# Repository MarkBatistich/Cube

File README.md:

# Cube

## Dynamic Model

To start, I drew a model of the sytem and defined some variables.

$\theta_w$ - angle of the wheel

$\theta_f$ - angle of the frame

$T$ - motor torque

$C_w$ - motor friction torque coefficient

$C_f$ - frame friction torque coefficient

$F_w$ - force of gravity on the wheel

$F_f$ - force of gravity on the frame

$I_c^o$ - moment of inertia of the cube about the origin

$I_w$ - moment of inertia of the wheel about its center of mass

$M_c^o$ - moment on the cube about the origin

$M_w$ - moment of the wheel about its center of mass

$m_w$ - mass of the wheel

$m_f$ - mass of the frame

$m_c$ - mass of the cube

$l_w$ - distance between the wheel's center of mass and the origin

$l_f$ - distance between the frame's center of mass and the origin

$l_c$ - distance between the cube's center of mass and the origin

I also defined the intertial axis such that +x is parellel to an unsloped surface and parallel to the cube face, +y is normal to an unsloped surface in the opposite direction as the force of gravity, and +z is in the direction of counterclockwise (CCW) wheel rotation. The origin O is placed at the corner of the cube touching the surface.

The equations of motion are constructed from the moments.

$M_c^o = I_c^o\ddot{\theta}_f = m_cl_cgsin(\theta_f) - (T - C_w\dot{\theta_w})-C_f\dot{\theta}_f$

$M_w = I_w(\ddot{\theta}_f+\ddot{\theta}_w) = T-C_w\dot{\theta_w}$

The cube moment of inertia about the origin can be found from the parallel axis theorem.

$I_c^o = I_f^o + I_w^o = I_f+m_fl_f^2 + I_w+m_wl_w^2$

The moment equations are solved for angular acceleration

$\ddot{\theta}_f = \frac{m_cl_cgsin(\theta_f)-T+C_w\dot{\theta_w}-C_f\dot{\theta}_f}{I_c^o}$

$\ddot{\theta}_w = \frac{T- C_w\dot{\theta_w}}{I_w} - \ddot{\theta}f$

From these equations, a state space model is made:

$x_1=\theta_f, x_2=\dot{\theta}_f,x_3=\dot{\theta}_w$

\dot{x}_1 = x_2$

$\dot{x}_2 = \frac{m_cl_cgsin(\theta_f)-T+C_w\dot{\theta_w}-C_f\dot{\theta}_f}{I_c^o}$

$\dot{x}_3 = \frac{T- C_w\dot{\theta_w}}{I_w} - \frac{m_cl_cgsin(\theta_f)-T+C_w\dot{\theta_w}-C_f\dot{\theta}_f}{I_c^o}$

The small angle approximation is applied: $\sin({\theta}_f)={\theta}_f$

The torque is related to the pwm input $u$ by the equation:

$T = K_tu$

where $K_t$ is the motor torque constant and $u$ is the applied PWM input to the motor on the range of $[-1, 1]$.

The state space equations are put into matrix form:

$\begin{bmatrix}
\dot{x}_1 \cr
\dot{x}_2 \cr
\dot{x}_3 
\end{bmatrix} = 
\begin{bmatrix}
0 & 1 & 0\cr
\frac{m_cl_cg}{I_c^o} & -\frac{C_f}{I_c^o} & \frac{C_w}{I_c^o}\cr
-\frac{m_cl_cg}{I_c^o} & \frac{C_f}{I_c^o} & -\frac{C_w}{I_w}-\frac{C_w}{I_c^o}
\end{bmatrix}
\begin{bmatrix}
x_1 \cr
x_2 \cr
x_3 
\end{bmatrix} + 
\begin{bmatrix}
0 \\
-\frac{K_t}{I_c^o} \\
\frac{K_t}{I_w}-\frac{K_t}{I_c^o}
\end{bmatrix} u $

Now all these values had to be determined. For better scaling, the gcs units were used (grams, centimeters, seconds):

$ g = 981 [\frac{cm}{s^2}]$

$m_c = 710\ [g]$

$l_c = 6.28\ [cm]$

$I_c^o = 37200\ [g*cm^2]$

$I_w = 2740 \ [g*cm^2]$

$C_f = 0$

$C_w = 0$

$K_t = 250000\ [\frac{g*cm^2}{s^2}]$

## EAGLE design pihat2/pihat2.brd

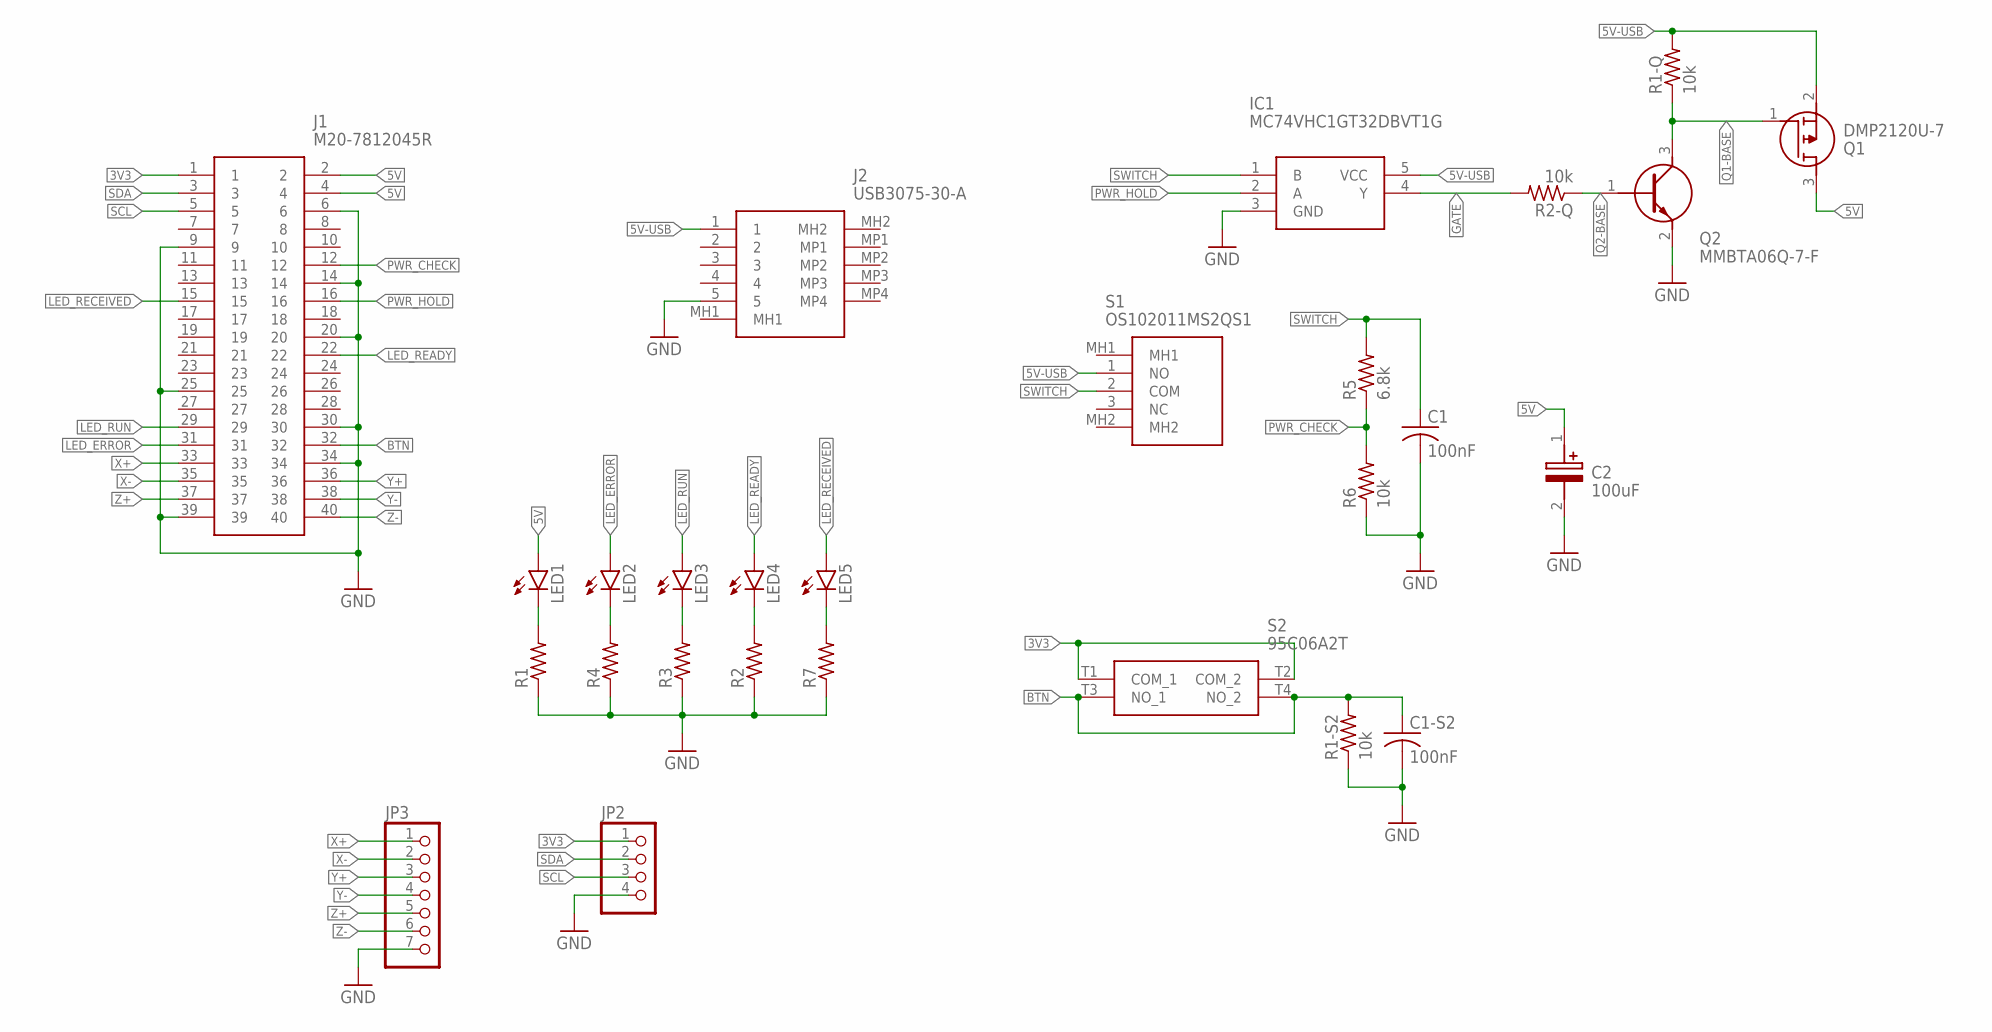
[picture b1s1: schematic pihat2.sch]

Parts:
C1, C1-S2: 100nF; C0805
C2: 100uF; CAPPRD250W45D630H500
IC1: MC74VHC1GT32DBVT1G
J1: M20-7812045R; M207812045R
J2: USB3075-30-A; USB307530A
JP2: PINHD-1X4; 1X04
JP3: PINHD-1X7; 1X07
LED1, LED2, LED3, LED4, LED5: LED5MM
Q1: DMP2120U-7; SOT96P240X110-3N
Q2: MMBTA06Q-7-F; SOT95P240X120-3N
R1, R2, R3, R4, R7: R-US_R0805; R0805
R1-Q, R1-S2, R2-Q, R6: 10k; R0805
R5: 6.8k; R0805
S1: OS102011MS2QS1
S2: 95C06A2T

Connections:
3V3: J1.1, JP2.1, S2.T1 (COM_1), S2.T2 (COM_2)
5V: C2.1 (+), J1.2, J1.4, LED1.A, Q1.3 (D)
5V-USB: IC1.5 (VCC), J2.1, Q1.2 (S), R1-Q.2, S1.1 (NO)
BTN: C1-S2.1, J1.32, R1-S2.2, S2.T3 (NO_1), S2.T4 (NO_2)
GATE: IC1.4 (Y), R2-Q.2
GND: C1.2, C1-S2.2, C2.2 (-), IC1.3 (GND), J1.6, J1.9, J1.14, J1.20, J1.25, J1.30, J1.34, J1.39, J2.5, JP2.4, JP3.7, Q2.2 (E), R1.1, R1-S2.1, R2.1, R3.1, R4.1, R6.1, R7.1
LED_ERROR: J1.31, LED2.A
LED_READY: J1.22, LED4.A
LED_RECEIVED: J1.15, LED5.A
LED_RUN: J1.29, LED3.A
unnamed: LED1.K (C), R1.2
unnamed: LED2.K (C), R4.2
unnamed: LED3.K (C), R3.2
unnamed: LED4.K (C), R2.2
unnamed: LED5.K (C), R7.2
PWR_CHECK: J1.12, R5.1, R6.2
PWR_HOLD: IC1.2 (A), J1.16
Q1-BASE: Q1.1 (G), Q2.3 (C), R1-Q.1
Q2-BASE: Q2.1 (B), R2-Q.1
SCL: J1.5, JP2.3
SDA: J1.3, JP2.2
SWITCH: C1.1, IC1.1 (B), R5.2, S1.2 (COM)
X+: J1.33, JP3.1
X-: J1.35, JP3.2
Y+: J1.36, JP3.3
Y-: J1.38, JP3.4
Z+: J1.37, JP3.5
Z-: J1.40, JP3.6

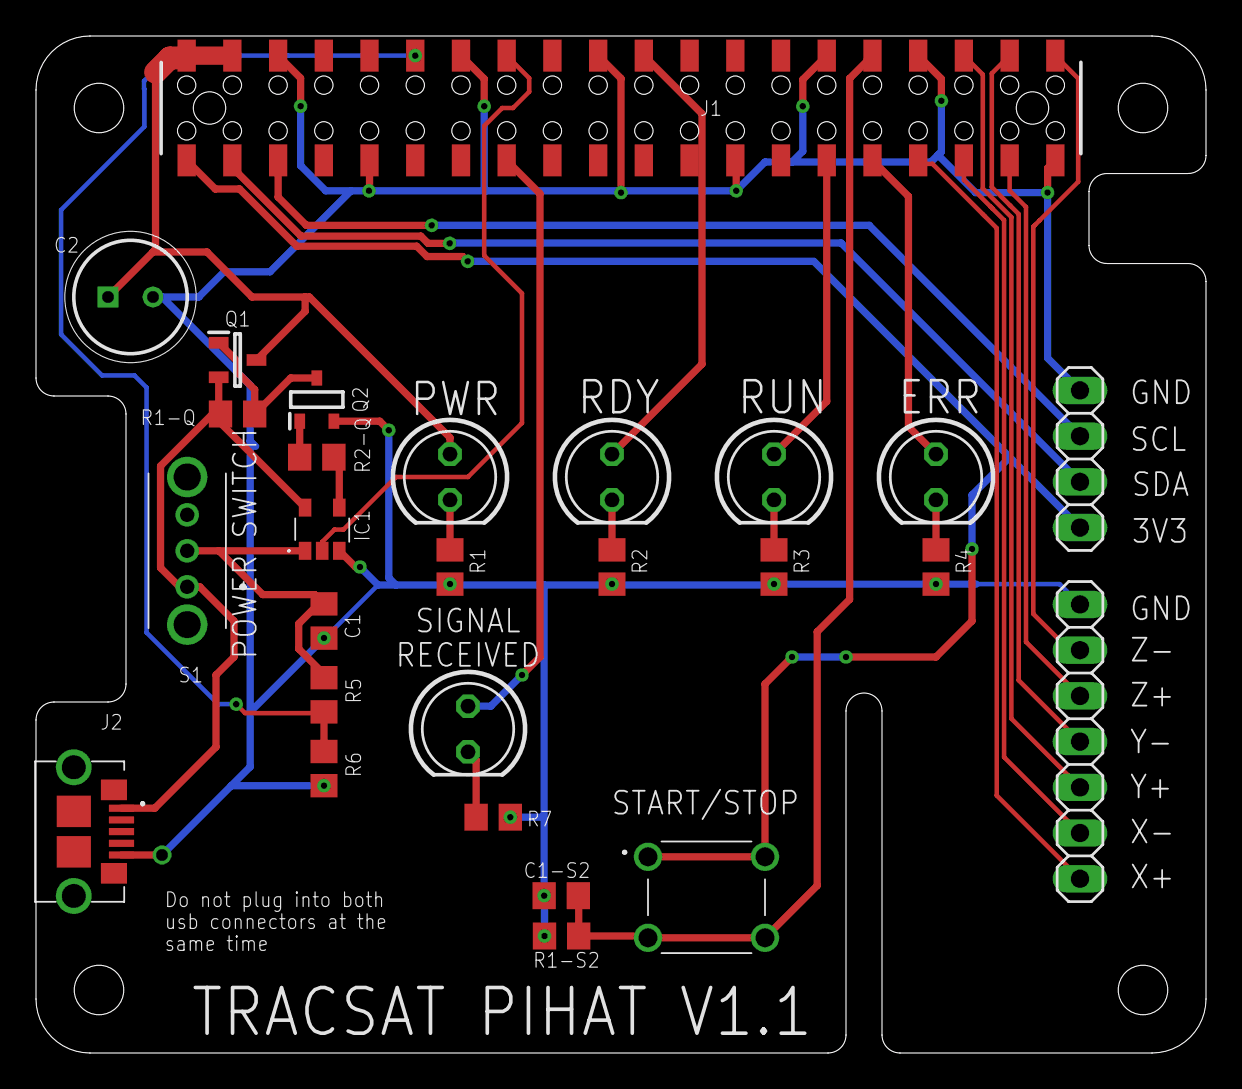
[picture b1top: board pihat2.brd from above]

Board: 2 copper layers, 65.0 x 56.5 mm, 27 parts (0 on the bottom side), 28 nets.

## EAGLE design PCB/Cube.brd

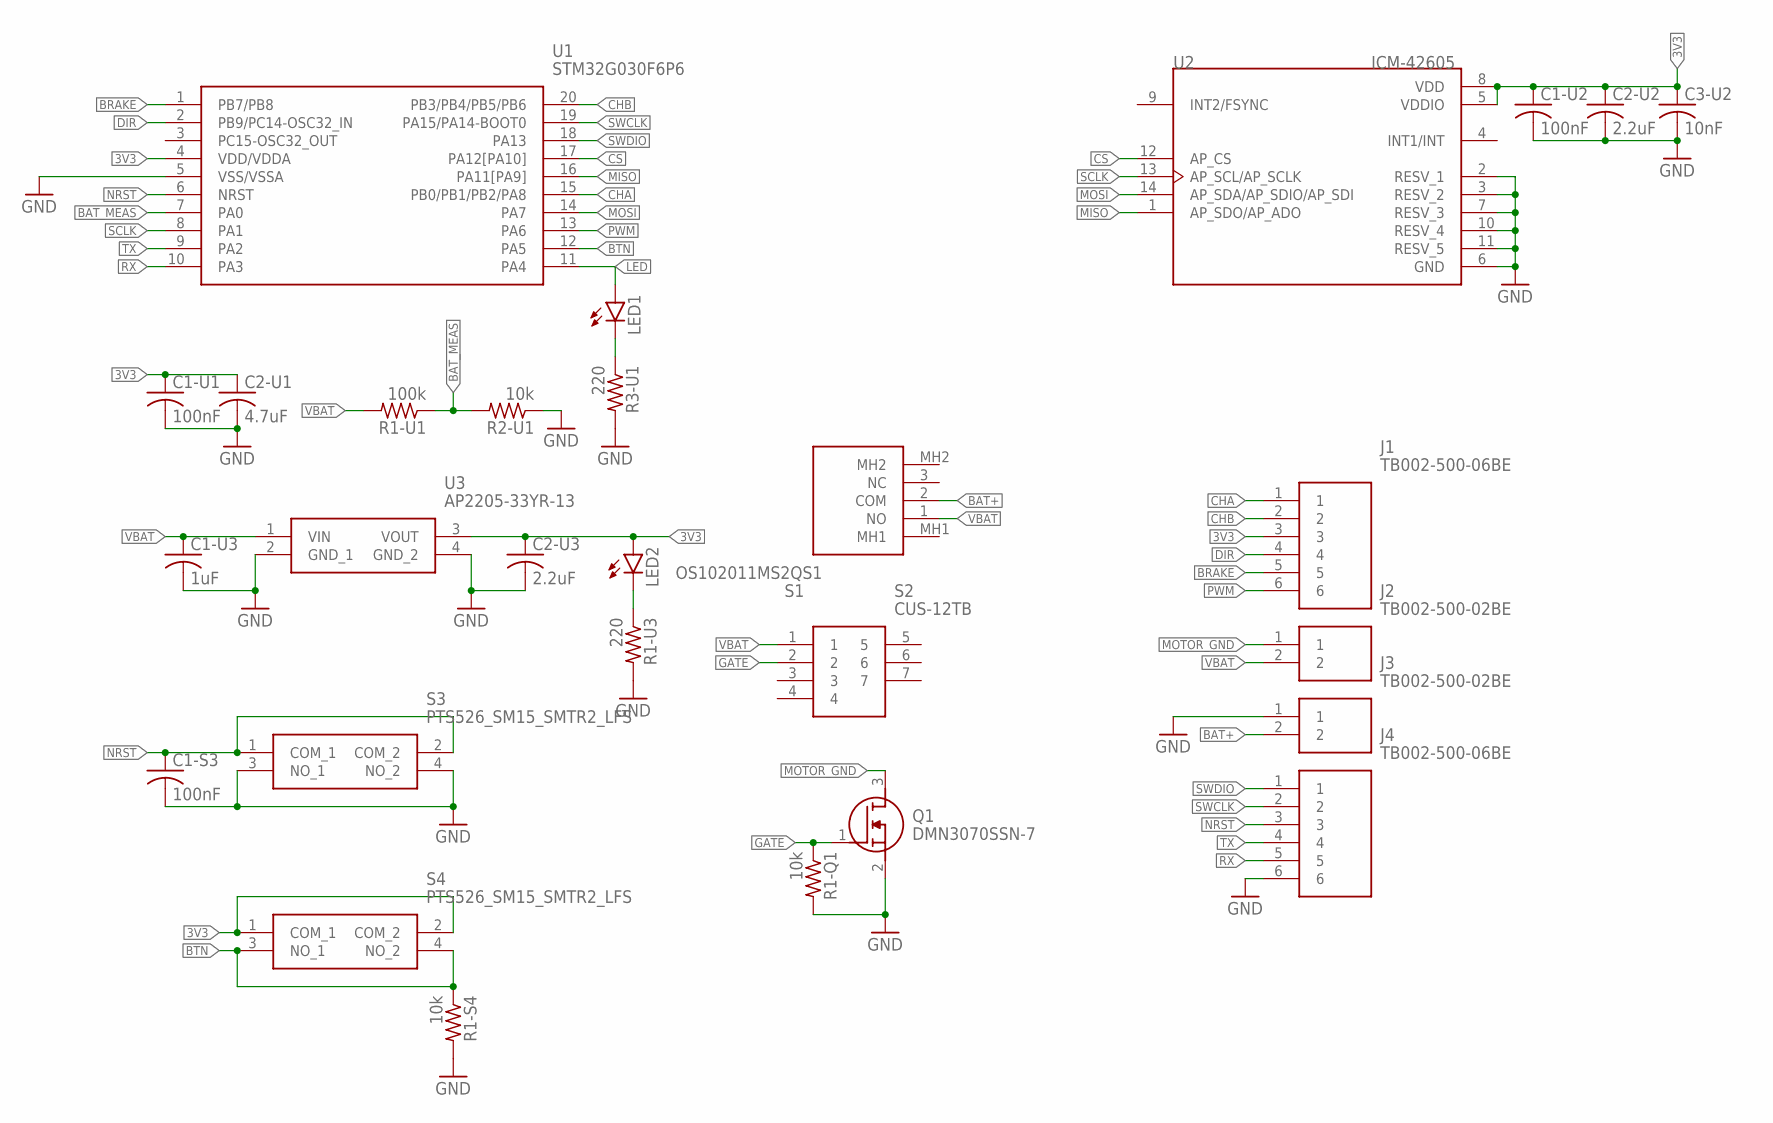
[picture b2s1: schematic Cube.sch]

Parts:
C1-S3, C1-U1, C1-U2: 100nF; C0805
C1-U3: 1uF; C0805
C2-U1: 4.7uF; C0805
C2-U2, C2-U3: 2.2uF; C0805
C3-U2: 10nF; C0805
J1, J4: TB002-500-06BE; TB00250006BE
J2, J3: TB002-500-02BE; TB00250002BE
LED1, LED2: LEDCHIP-LED0805; CHIP-LED0805
Q1: DMN3070SSN-7; SOT95P285X140-3N
R1-Q1, R1-S4, R2-U1: 10k; R0805
R1-U1: 100k; R0805
R1-U3, R3-U1: 220; R0805
S1: OS102011MS2QS1
S2: CUS-12TB; CUS-12B
S3, S4: PTS526_SM15_SMTR2_LFS; PTS526SM15SMTR2LFS
U1: STM32G030F6P6; SOP65P640X120-20N
U2: ICM-42605; PQFN50P300X250X97-14N
U3: AP2205-33YR-13; AP220533YR13

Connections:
3V3: C1-U1.1, C1-U2.1, C2-U1.1, C2-U2.1, C2-U3.1, C3-U2.1, J1.3, LED2.A, S4.1 (COM_1), S4.2 (COM_2), U1.4 (VDD/VDDA), U2.5 (VDDIO), U2.8 (VDD), U3.3 (VOUT)
BAT+: J3.2, S1.2 (COM)
BAT_MEAS: R1-U1.1, R2-U1.2, U1.7 (PA0)
BRAKE: J1.5, U1.1 (PB7/PB8)
BTN: R1-S4.1, S4.3 (NO_1), S4.4 (NO_2), U1.12 (PA5)
CHA: J1.1, U1.15 (PB0/PB1/PB2/PA8)
CHB: J1.2, U1.20 (PB3/PB4/PB5/PB6)
CS: U1.17 (PA12[PA10]), U2.12 (AP_CS)
DIR: J1.4, U1.2 (PB9/PC14-OSC32_IN)
GATE: Q1.1 (G), R1-Q1.1, S2.2
GND: C1-S3.2, C1-U1.2, C1-U2.2, C1-U3.2, C2-U1.2, C2-U2.2, C2-U3.2, C3-U2.2, J3.1, J4.6, Q1.2 (S), R1-Q1.2, R1-S4.2, R1-U3.2, R2-U1.1, R3-U1.2, S3.3 (NO_1), S3.4 (NO_2), U1.5 (VSS/VSSA), U2.2 (RESV_1), U2.3 (RESV_2), U2.6 (GND), U2.7 (RESV_3), U2.10 (RESV_4), U2.11 (RESV_5), U3.2 (GND_1), U3.4 (GND_2)
LED: LED1.A, U1.11 (PA4)
LED1-R: LED1.C, R3-U1.1
LED2-R: LED2.C, R1-U3.1
MISO: U1.16 (PA11[PA9]), U2.1 (AP_SDO/AP_ADO)
MOSI: U1.14 (PA7), U2.14 (AP_SDA/AP_SDIO/AP_SDI)
MOTOR_GND: J2.1, Q1.3 (D)
NRST: C1-S3.1, J4.3, S3.1 (COM_1), S3.2 (COM_2), U1.6 (NRST)
PWM: J1.6, U1.13 (PA6)
RX: J4.5, U1.10 (PA3)
SCLK: U1.8 (PA1), U2.13 (AP_SCL/AP_SCLK)
SWCLK: J4.2, U1.19 (PA15/PA14-BOOT0)
SWDIO: J4.1, U1.18 (PA13)
TX: J4.4, U1.9 (PA2)
VBAT: C1-U3.1, J2.2, R1-U1.2, S1.1 (NO), S2.1, U3.1 (VIN)

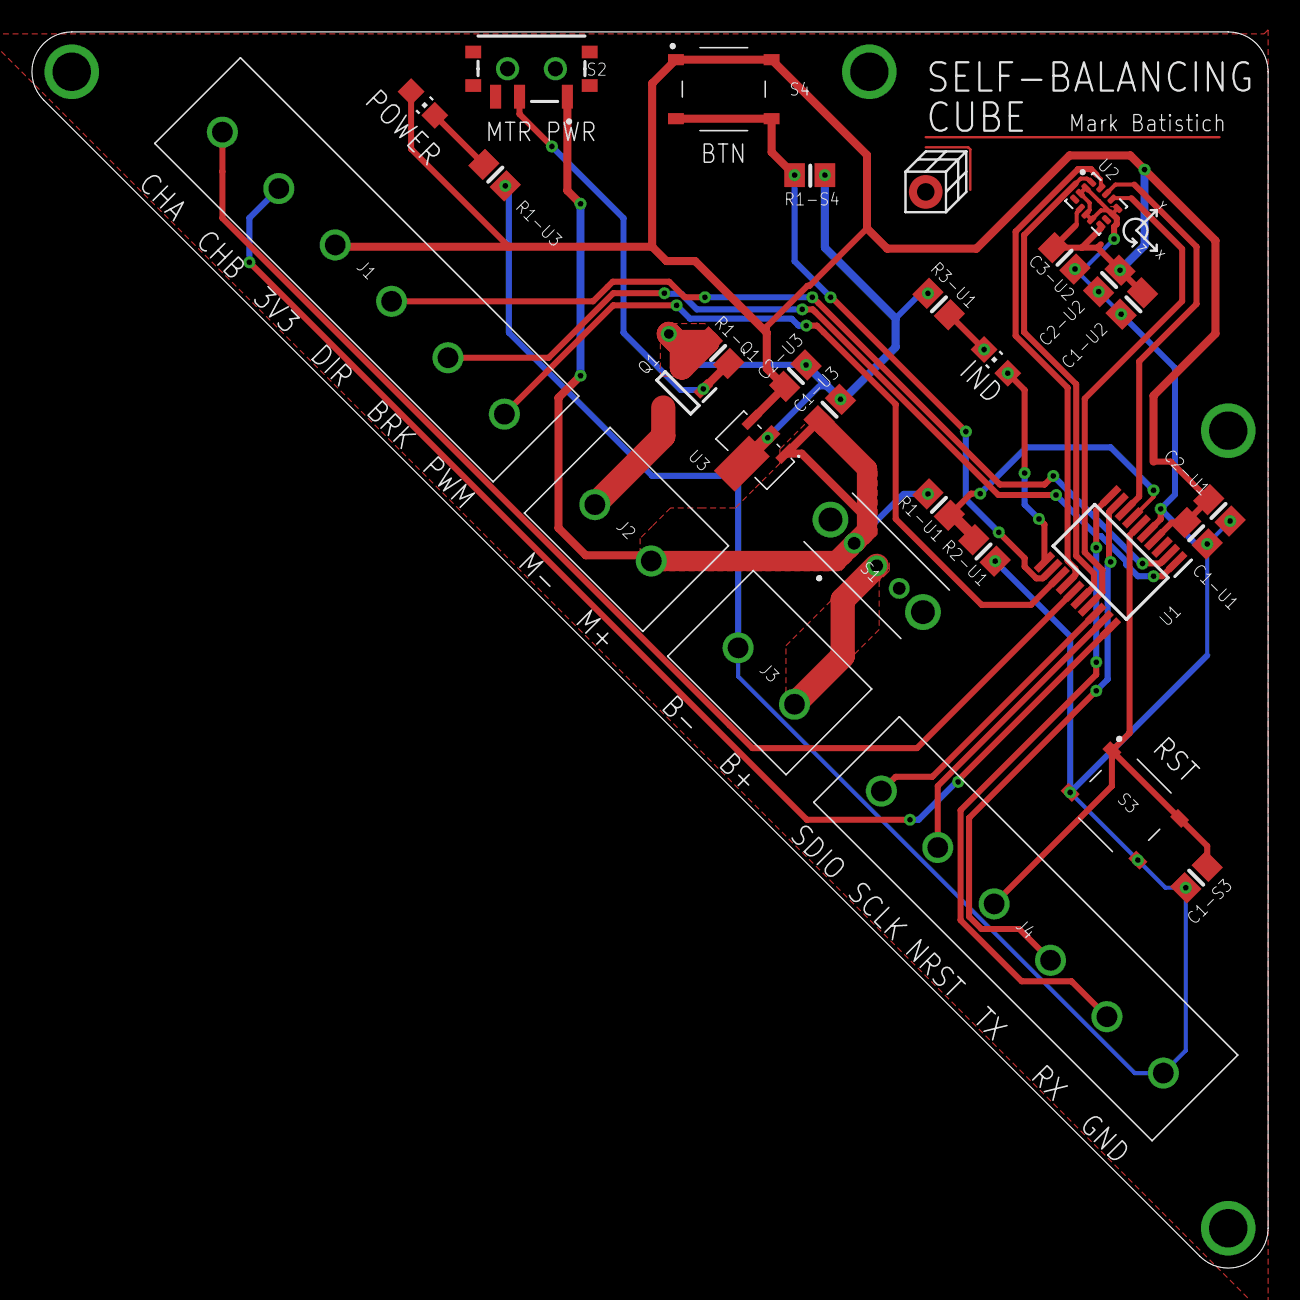
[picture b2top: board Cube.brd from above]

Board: 2 copper layers, 77.5 x 77.5 mm, 28 parts (0 on the bottom side), 25 nets.

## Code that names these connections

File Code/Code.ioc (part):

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Mcu.Name=STM32G030F6Px
Mcu.Package=TSSOP20
Mcu.UserName=STM32G030F6Px
PA0.GPIOParameters=GPIO_Label
PA0.GPIO_Label=BAT_MEAS
PA0.Mode=IN0
PA0.Signal=ADC1_IN0
PA1.Mode=Full_Duplex_Master
PA1.Signal=SPI1_SCK
PA11\ [PA9].Mode=Full_Duplex_Master
PA11\ [PA9].Signal=SPI1_MISO
PA12\ [PA10].GPIOParameters=GPIO_Label
PA12\ [PA10].GPIO_Label=CS
PA12\ [PA10].Signal=GPIO_Output
PA13.Mode=Serial_Wire
PA13.Signal=SYS_SWDIO
PA14-BOOT0.Mode=Serial_Wire
PA14-BOOT0.Signal=SYS_SWCLK
PA2.Mode=Asynchronous
PA2.Signal=USART2_TX
PA3.Mode=Asynchronous
PA3.Signal=USART2_RX
PA4.GPIOParameters=GPIO_Label
PA4.GPIO_Label=LED
PA4.Signal=GPIO_Output
PA5.GPIOParameters=GPIO_Label
PA5.GPIO_Label=BTN
PA5.Signal=GPIO_Input
PA6.Signal=S_TIM3_CH1
PA7.Mode=Full_Duplex_Master
PA7.Signal=SPI1_MOSI
PA8.Signal=S_TIM1_CH1
PB3.Signal=S_TIM1_CH2
PB8.GPIOParameters=GPIO_Label
PB8.GPIO_Label=BRAKE
PB8.Signal=GPIO_Output
PB9.GPIOParameters=GPIO_Label
PB9.GPIO_Label=DIR
PB9.Signal=GPIO_Output
RCC.HSE_VALUE=8000000
RCC.SYSCLKFreq_VALUE=16000000
board=custom

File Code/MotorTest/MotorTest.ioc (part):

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Mcu.Name=STM32F411R(C-E)Tx
Mcu.Package=LQFP64
Mcu.UserName=STM32F411RETx
PA13.GPIOParameters=GPIO_Label
PA13.GPIO_Label=TMS
PA13.Mode=Trace_Asynchronous_SW
PA13.Signal=SYS_JTMS-SWDIO
PA14.GPIOParameters=GPIO_Label
PA14.GPIO_Label=TCK
PA14.Mode=Trace_Asynchronous_SW
PA14.Signal=SYS_JTCK-SWCLK
PA2.GPIOParameters=GPIO_Label
PA2.GPIO_Label=USART_TX
PA2.Mode=Asynchronous
PA2.Signal=USART2_TX
PA3.GPIOParameters=GPIO_Label
PA3.GPIO_Label=USART_RX
PA3.Mode=Asynchronous
PA3.Signal=USART2_RX
PA5.GPIOParameters=GPIO_Label
PA5.GPIO_Label=LD2 [Green Led]
PA5.Signal=GPIO_Output
PA8.Signal=S_TIM1_CH1
PA9.Signal=S_TIM1_CH2
PB3.GPIOParameters=GPIO_Label
PB3.GPIO_Label=SWO
PB3.Mode=Trace_Asynchronous_SW
PB3.Signal=SYS_JTDO-SWO
PB4.Signal=S_TIM3_CH1
PB5.GPIOParameters=GPIO_Label
PB5.GPIO_Label=DIR
PB5.Signal=GPIO_Output
PC13-ANTI_TAMP.GPIOParameters=GPIO_Label,GPIO_ModeDefaultEXTI
PC13-ANTI_TAMP.GPIO_Label=B1 [Blue PushButton]
PC13-ANTI_TAMP.GPIO_ModeDefaultEXTI=GPIO_MODE_IT_FALLING
PC13-ANTI_TAMP.Signal=GPXTI13
PC14-OSC32_IN.Mode=LSE-External-Oscillator
PC14-OSC32_IN.Signal=RCC_OSC32_IN
PC15-OSC32_OUT.Mode=LSE-External-Oscillator
PC15-OSC32_OUT.Signal=RCC_OSC32_OUT
PH0\ -\ OSC_IN.Mode=HSE-External-Clock-Source
PH0\ -\ OSC_IN.Signal=RCC_OSC_IN
PH1\ -\ OSC_OUT.Mode=HSE-External-Clock-Source
PH1\ -\ OSC_OUT.Signal=RCC_OSC_OUT
RCC.HSE_VALUE=8000000
RCC.SYSCLKFreq_VALUE=50000000
RCC.SYSCLKSource=RCC_SYSCLKSOURCE_PLLCLK
board=NUCLEO-F411RE
boardIOC=true

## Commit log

2022-01-17 moved to github
2022-01-17 added code
2022-02-06 Updated code and models
2022-02-09 Code updates
2022-02-09 readme
2022-02-09 read
2022-02-09 test
2022-02-10 Code and readme development. Nearly stable cube
2022-02-15 stable code with long term balance
2022-02-15 readme update. Delete ipynb
2022-03-12 deleted extra code, adjusted pid, put pihat files in
